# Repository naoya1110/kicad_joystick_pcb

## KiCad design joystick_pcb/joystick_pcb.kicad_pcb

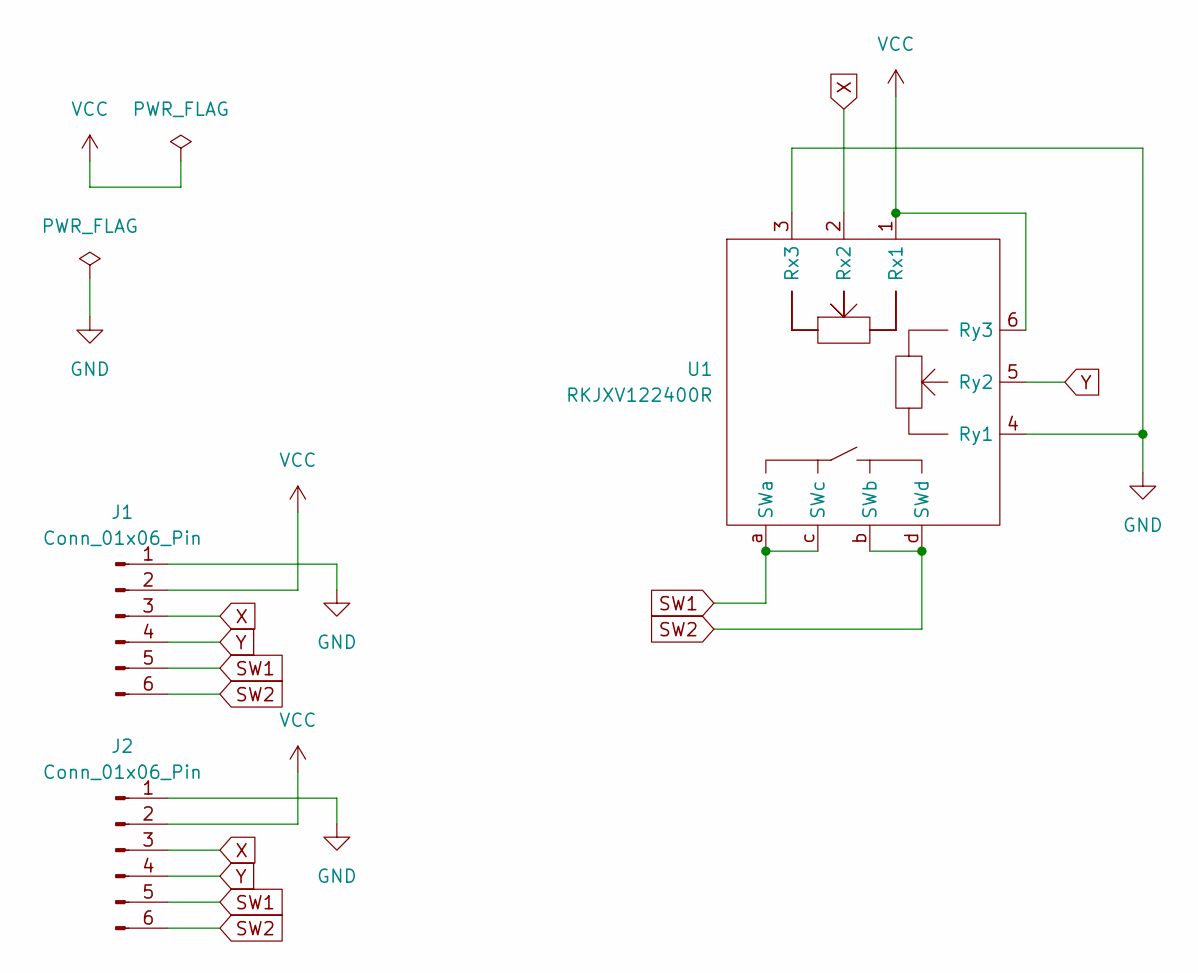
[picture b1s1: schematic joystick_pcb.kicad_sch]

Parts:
J1, J2: Conn_01x06_Pin; PinHeader_1x06_P2.54mm_Vertical
U1: RKJXV122400R

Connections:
GND: J1.1, J2.1, U1.3 (Rx3), U1.4 (Ry1)
SW1: J1.5, J2.5, U1.a (SWa), U1.c (SWc)
SW2: J1.6, J2.6, U1.b (SWb), U1.d (SWd)
VCC: J1.2, J2.2, U1.1 (Rx1), U1.6 (Ry3)
X: J1.3, J2.3, U1.2 (Rx2)
Y: J1.4, J2.4, U1.5 (Ry2)

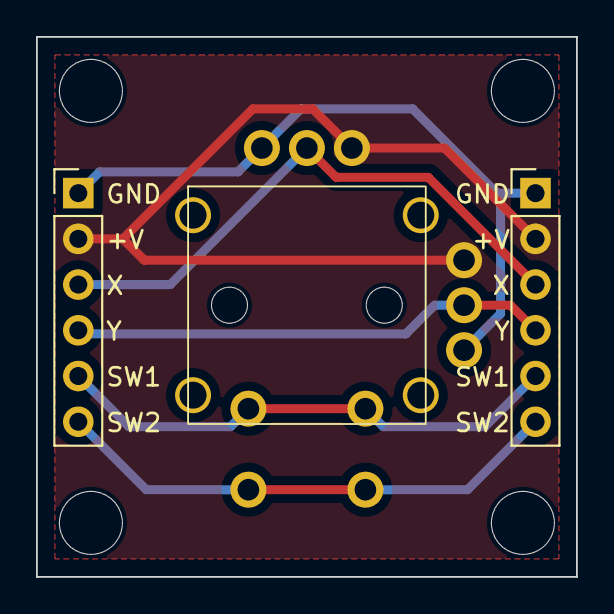
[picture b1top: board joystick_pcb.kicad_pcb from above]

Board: 2 copper layers, 30.0 x 30.0 mm, 3 parts (0 on the bottom side), 6 nets.
